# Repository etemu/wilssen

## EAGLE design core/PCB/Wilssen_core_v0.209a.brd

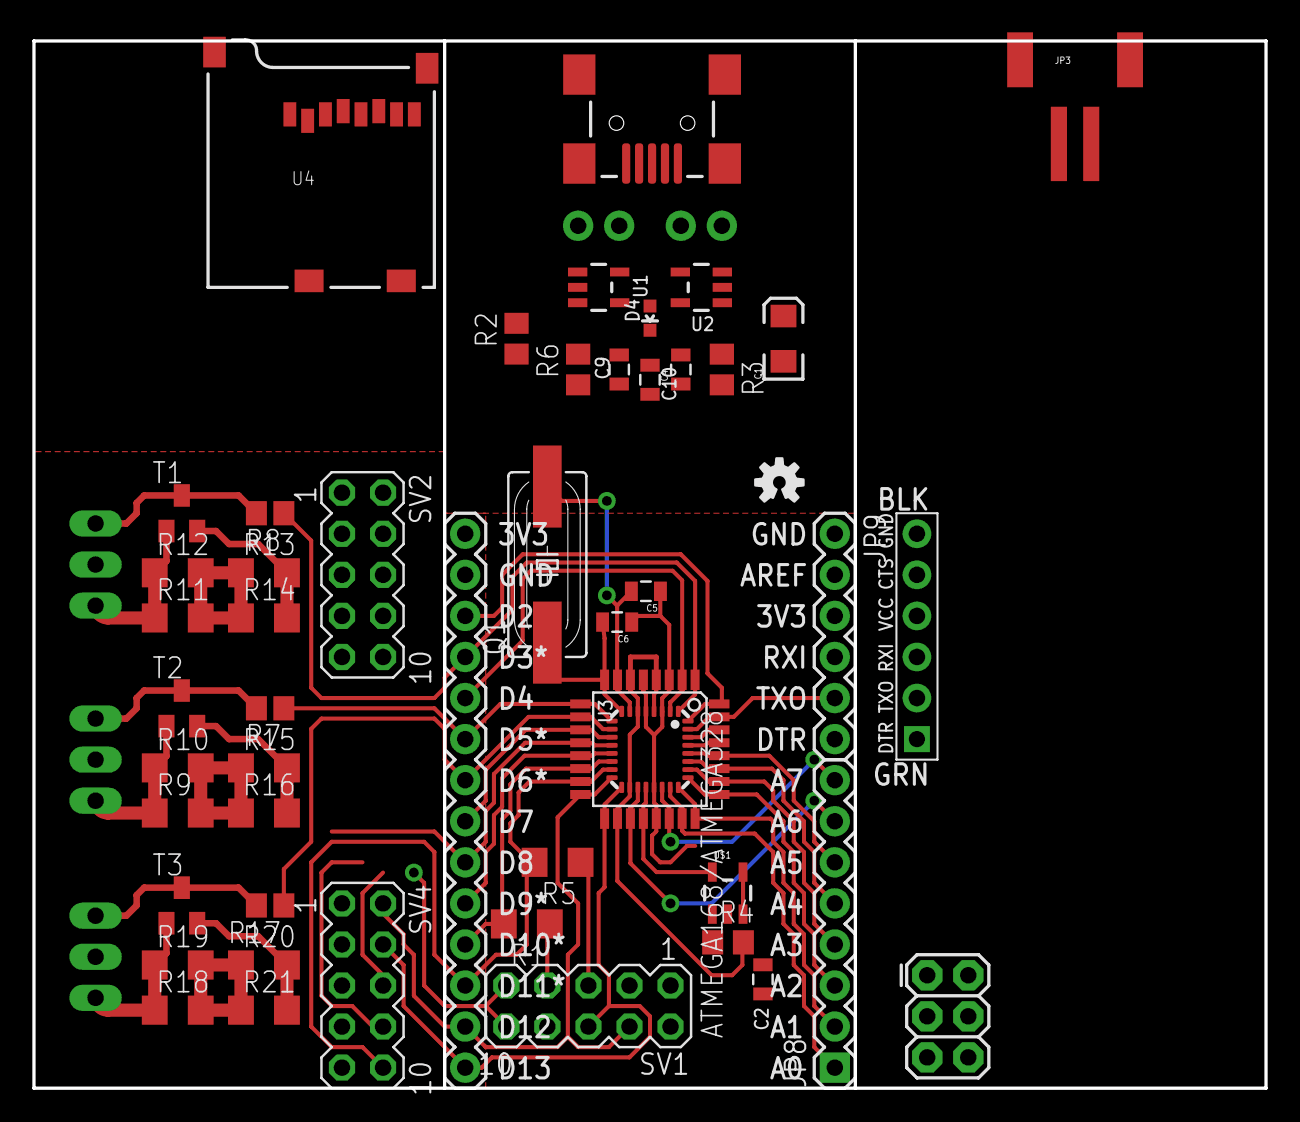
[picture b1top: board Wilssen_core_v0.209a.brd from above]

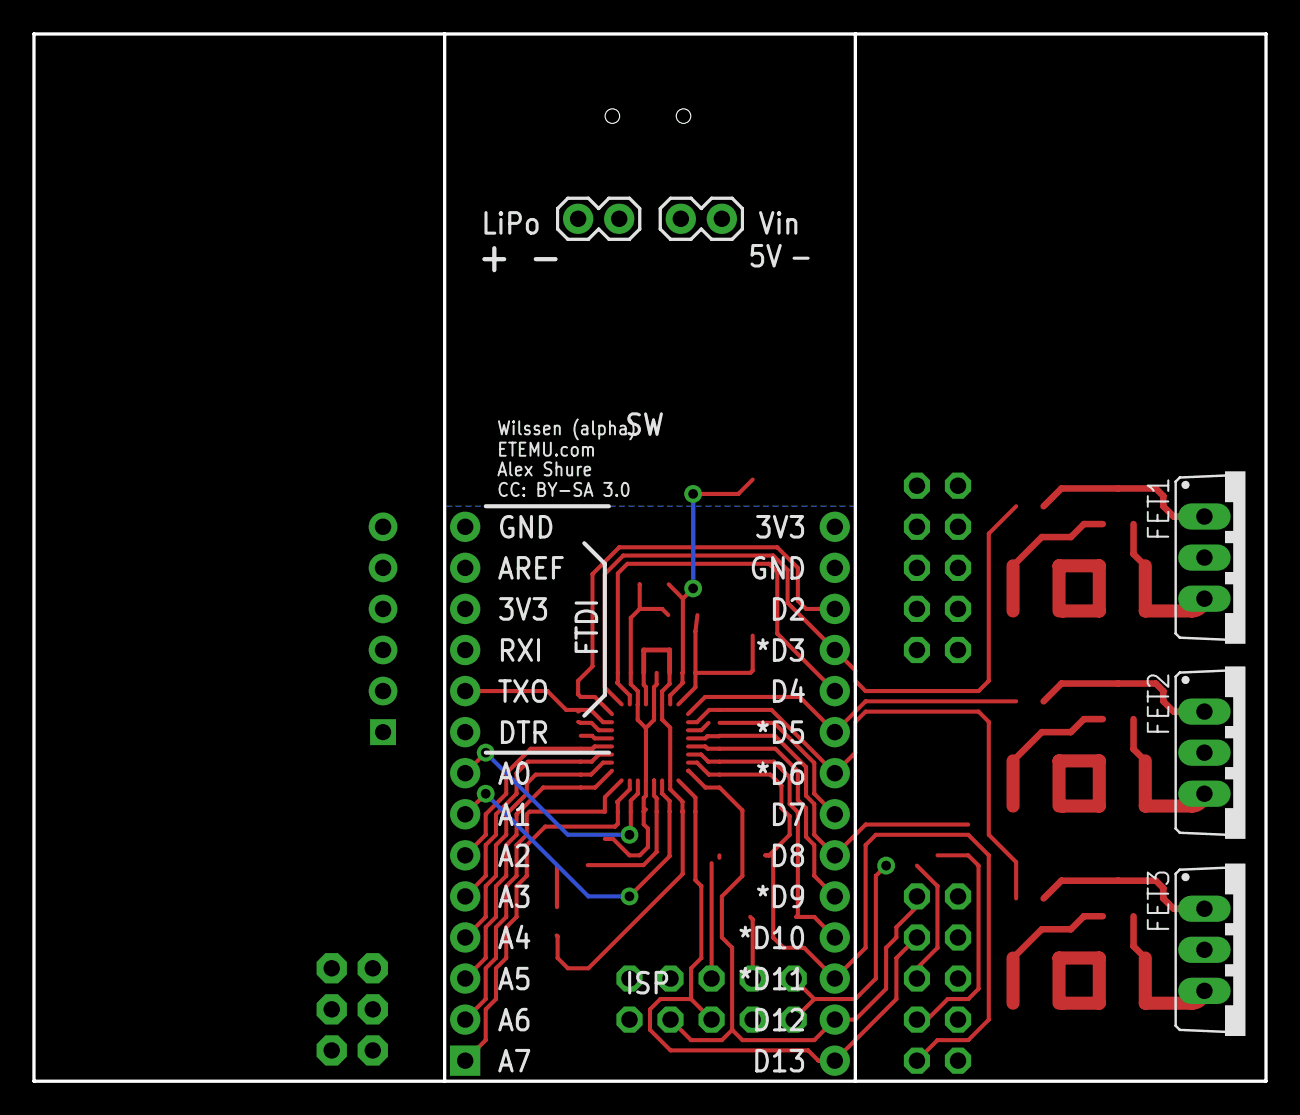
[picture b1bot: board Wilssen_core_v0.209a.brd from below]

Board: 2 copper layers, 76.2 x 64.8 mm, 56 parts (5 on the bottom side), 43 nets.

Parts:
ATMEGA168/ATMEGA328: MEGA8-MI; MLF32
C1: 10uF; EIA3216
C2, C4: 0.1uF; 0805
C5, C6: 22nF; 0805
C9, C10: 1.0uF; 0805
CC_TEXT1: CREATIVE_COMMONS
D4: Yellow; LED-0603
FET1, FET2, FET3: IRLZ; TO220BV
JP1: M14; 1X14
JP2, JP6: 1X02
JP3: S2B-PH
JP4: AVR_SPI; 2X3
JP5: FTDI_DEVICE; FTDI_DEVICE_SIDE
JP8: 1X08
JP9: 1X06
LOGO1: OSHW-LOGOS; OSHW-LOGO-S
Q1: 8Mhz; SM49
R1, R5, R9, R10, R11, R12, R13, R14, R15, R16, R18, R19, R20, R21: 3R3; R1206
R2: 470k; R0805
R3: 1M; R0805
R4, R7, R8, R17: 10k; R0805
R6: 1k; R0805
SV1, SV2, SV4: MA05-2
T1, T2, T3: BC849; SOT23
U1: MAX1555; SOT23-5
U2: 3.3V; SOT23-5
U3: ATMEGA168/ATMEGA328; TQFP32-08
U4: USD-SOCKETNEW; MICRO-SD-SOCKET-PP
U$1: LM4128-2.5VREF; SOT23-5
X1: USBSMD; USB-MINIB

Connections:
A0: ATMEGA168/ATMEGA328.23, C4.2, JP8.1, R2.2, R3.1, U3.23
A1: ATMEGA168/ATMEGA328.24, JP8.2, U3.24
A2: ATMEGA168/ATMEGA328.25, JP8.3, U3.25
A3: ATMEGA168/ATMEGA328.26, JP8.4, U3.26
A4: ATMEGA168/ATMEGA328.27, JP8.5, U3.27
A5: ATMEGA168/ATMEGA328.28, JP8.6, U3.28
A6: ATMEGA168/ATMEGA328.19, JP8.7, U3.19
A7: ATMEGA168/ATMEGA328.22, JP8.8, U3.22
AREF: ATMEGA168/ATMEGA328.20, JP9.2, U3.20, U$1.5
CSN: SV2.8, SV4.8
CSN_NRF24: R1.1, SV1.7
D2: ATMEGA168/ATMEGA328.32, JP1.3, U3.32
D3_LED-R: ATMEGA168/ATMEGA328.1, JP1.4, R8.1, U3.1
D4: ATMEGA168/ATMEGA328.2, JP1.5, U3.2
D5_LED-G: ATMEGA168/ATMEGA328.9, JP1.6, R7.1, U3.9
D6_LED-B: ATMEGA168/ATMEGA328.10, JP1.7, R17.1, U3.10
D7: ATMEGA168/ATMEGA328.11, JP1.8, U3.11
D8: ATMEGA168/ATMEGA328.12, JP1.9, U3.12
D9_CSN_SD: ATMEGA168/ATMEGA328.13, JP1.10, U3.13, U4.2
D10_CSN_NRF24: ATMEGA168/ATMEGA328.14, JP1.11, R1.2, U3.14
GATE1: FET1.G, R8.2, T1.3
GATE2: FET2.G, R7.2, T2.3
GATE3: FET3.G, R17.2, T3.3
GND: ATMEGA168/ATMEGA328.3, ATMEGA168/ATMEGA328.5, ATMEGA168/ATMEGA328.21, C1.C, C2.2, C4.1, C5.1, C6.1, C9.2, C10.2, JP1.2, JP2.1, JP3.1, JP4.6, JP6.1, JP9.1, R2.1, R13.2, R14.2, R15.2, R16.2, R20.2, R21.2, SV1.1, SV1.2, SV4.1, SV4.3, SV4.5, SV4.7, T1.2, T2.2, T3.2, U1.2, U2.2, U3.3, U3.5, U3.21, U4.6, U4.CD1, U4.CD2, U4.GND1, U4.GND3, U$1.2, X1.GND
MISO: ATMEGA168/ATMEGA328.16, JP1.13, JP4.1, SV1.4, SV2.2, SV4.2, U3.16
MOSI: ATMEGA168/ATMEGA328.15, JP1.12, JP4.4, R5.2, SV2.10, SV4.10, U3.15
unnamed: D4.C, R6.1
unnamed: R6.2, U1.3
NS$1: R11.2, R12.2, R13.1, R14.1
NS$2: R9.2, R10.2, R15.1, R16.1
NS$3: R18.2, R19.2, R20.1, R21.1
RST: ATMEGA168/ATMEGA328.29, JP4.5, R4.1, SV2.6, SV4.6, U3.29
RXI: ATMEGA168/ATMEGA328.30, JP9.4, U3.30
SCK: ATMEGA168/ATMEGA328.17, JP1.14, JP4.3, SV1.6, SV2.4, SV4.4, U3.17, U4.5
SRC1: FET1.S, R11.1, R12.1, T1.1
SRC2: FET2.S, R9.1, R10.1, T2.1
SRC3: FET3.S, R18.1, R19.1, T3.1
TXO: ATMEGA168/ATMEGA328.31, JP9.5, U3.31
USB_VIN: C9.1, JP6.2, U1.4, X1.VBUS
VBATT: C10.1, D4.A, JP2.2, JP3.2, R3.2, U1.5, U2.1, U2.3
VCC: ATMEGA168/ATMEGA328.4, ATMEGA168/ATMEGA328.6, ATMEGA168/ATMEGA328.18, C1.A, C2.1, JP1.1, JP4.2, JP9.3, R4.2, SV1.9, SV1.10, SV4.9, U2.5, U3.4, U3.6, U3.18, U4.4, U$1.3, U$1.4
XTAL1: ATMEGA168/ATMEGA328.7, C5.2, Q1.2, U3.7
XTAL2: ATMEGA168/ATMEGA328.8, C6.2, Q1.1, U3.8

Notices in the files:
parts and their libraries:
SparkFun-Connectors: Licensing: CC v3.0 Share-Alike You are welcome to use this library for commercial purposes.
SparkFun-Aesthetics: Released under the Creative Commons Attribution Share-Alike 3.0 License
SparkFun-Aesthetics: http://creativecommons.org/licenses/by-sa/3.0
